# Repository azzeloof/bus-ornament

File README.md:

# London Bus Ornament
 A PCB holiday ornament with lots of blinking LEDs!

## Hardware
The board consists of twelve reverse-mounted LEDs [charlieplexed](https://en.wikipedia.org/wiki/Charlieplexing) and hooked up to an ATtiny85. Each LED is individually addressable, even though only four of the ATtiny's pins are being used (Charlieplexing is magic)! The board also has a pushbutton for switching between modes. The ornament is powered via two CR2025 batteries which feed a 3.3V buck converter.

The design works as-is, but there's an issue. When the programmer is hooked up, it needs to be set to not power the PCB. If it does power the boar,d it will immediatley fry the buck converter. To get around this, I cut the VCC trace to the ICSP and connected that pin to the unused pin of the power switch via a bodged wire. 

## Firmware
The ATtiny is programmed using the PlatformIO framework. Before programming, you need to write an Arduino bootloader to the chip using the Arduino IDE. When burning the bootloader, here are the settings we used:

+ Chip: "ATtiny85" (from the ATtiny Core board library)
+ Clock: "8 MHz (internal)"
+ B.O.D: "B.O.D. Disabled"
+ Timer 1 Clock: "CPU"
+ LTO (1.6.11+ only): "Disabled"

The code is adapted from the wonderful work of David Johnson-Davies, published at http://www.technoblogy.com/show?2H0K.

To program the chips, we used SparkFun's [Pocket AVR Programmer](https://www.sparkfun.com/products/9825), but you should be able to use any programmer compatibe with the ATtiny85 (or just use an Arduino Uno!).

## Version History
Release 1.0 will represent the bus ornaments as we initially made and distributed them. Once it is released, maybe we'll improve some stuff (but any hardware improvements will be untested).

## Warning
Electricity creates heat, and excess heat around something like a Christmas tree can cause big problems. Use at your own risk! The designs here have only been minimally tested and are absolutley not guarenteed to be safe.

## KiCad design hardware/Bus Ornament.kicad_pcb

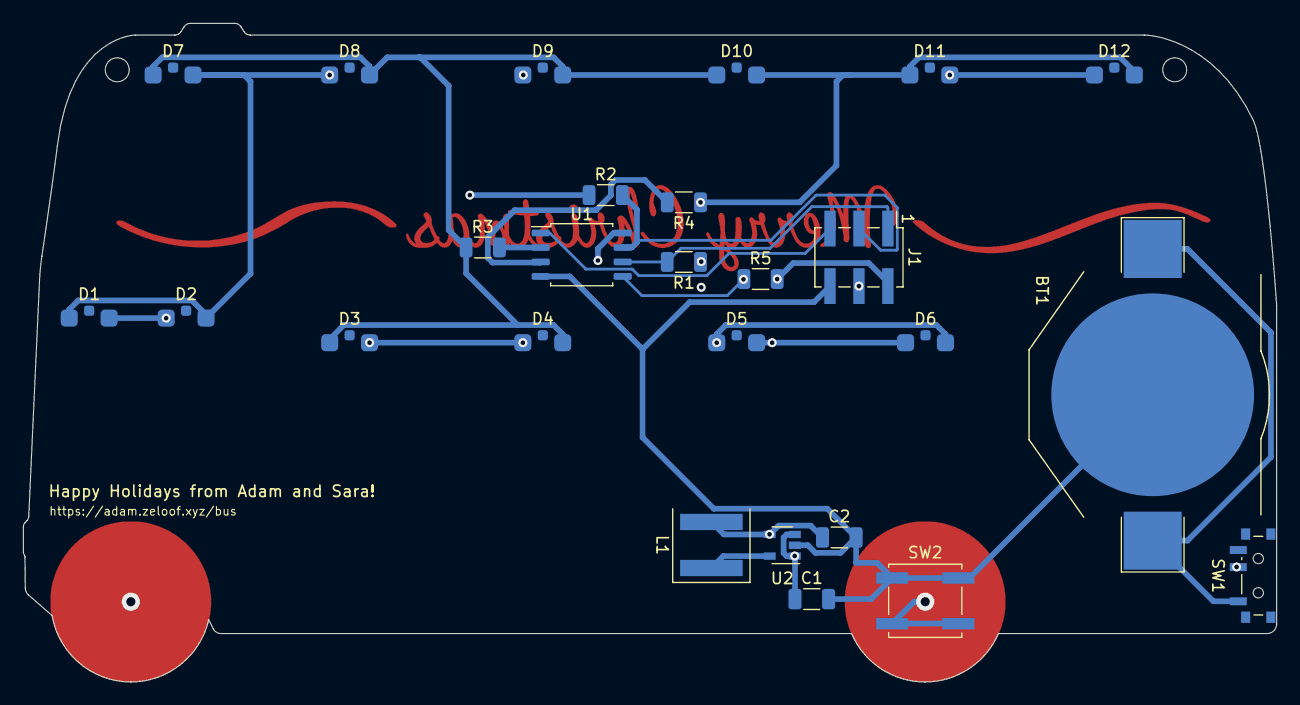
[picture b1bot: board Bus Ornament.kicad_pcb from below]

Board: 4 copper layers, 110.0 x 57.8 mm, 26 parts (26 on the bottom side), 15 nets.

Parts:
BT1: Battery; BatteryHolder_Keystone_3002_1x2032
C1, C2: C; C_1206_3216Metric
D1, D2, D3, D4, D5, D6, D7, D8, D9, D10, D11, D12: LED; IN-S121AS
J1: Conn_02x03_Odd_Even; PinHeader_2x03_P2.54mm_Vertical_SMD
L1: L; L_Coilcraft_XAL60xx_6.36x6.56mm
R1, R2, R3, R4, R5: R_US; R_1206_3216Metric
SW1: SW_SPST; SW_SPDT_PCM12
SW2: SW_Push; SW_Push_1P1T_NO_CK_KSC6xxJ
U1: ATtiny85-20PU; SOIC-8_5.23x5.23mm_P1.27mm
U2: TPS62203DBV; SOT-23-5

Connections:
+BATT: BT1.1, SW1.1
GND: BT1.2, C1.2, C2.2, J1.6, SW2.2, U1.4, U2.2
MISO: J1.1, R1.2, U1.6
MOSI: J1.4, R5.1, SW2.1, U1.5
unnamed: C1.1, SW1.2, U2.1, U2.3
unnamed: D1.1, D2.2, D7.2, D8.1, D11.2, D12.1, R2.1
unnamed: D1.2, D2.1, D3.2, D4.1, D5.2, D6.1, R1.1
unnamed: D3.1, D4.2, D7.1, D8.2, D9.2, D10.1, R3.1
unnamed: D5.1, D6.2, D9.1, D10.2, D11.1, D12.2, R4.1
unnamed: L1.1, U2.5
unnamed: R3.2, U1.2
unnamed: R4.2, U1.3
RST: J1.5, U1.1
SCK: J1.3, R2.2, U1.7
VCC: C2.1, J1.2, L1.2, R5.2, U1.8, U2.4

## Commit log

2021-11-19 Design completed
2021-11-19 Generated gerbers
2021-11-19 Repo Reorg and Cleanup
2021-11-26 Firmware written but untested
2021-11-27 Minor firmware tweaks, mostly working
    Tested on menorah hardware
2021-12-13 Crated front fill, ordered new boards
2021-12-22 Documentation and firmware
